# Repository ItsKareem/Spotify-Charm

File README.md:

# Spotify Charm ⋆ ݁ ♫ .

note: I still haven't done the Spotify API code for this. I just shipped it now for the [Arcana](https://arcana.hackclub.com/) deadline.

This Spotify Charm is a palm-sized, fully functional hardware display and controller that uses Spotify, designed with a retro aesthetic inspired by old-school MP3 players. I want to built this irl and use clay and paint to gice it a seashell shap and use actual seashells and use custom jewelery and bead kits to make it an actual charm. I feel like it would be fun to use this instead of my phone. I was inspired by online videos of people making their own creative hardware and physical media projects!

## Features
- Wemos ESP32-C3 Mini development board acting as the main controller
- Rotary Encoder for volume control
- Triple Button Layout ◁ㅤ ❚❚ ㅤ▷ (+ a power switch)
- uses a LiPo Battery Support with full power management circuitry
- Custom 3D-Printed Case featuring a 9cm diameter circular design

### 3D Case:

### Front:

### Back:

### PCB:

### Schematic (1. Baterry Management):

### Schematic (2. Push Buttons and Rotary Encoder):

### Schematic (3. ESP32 C3):

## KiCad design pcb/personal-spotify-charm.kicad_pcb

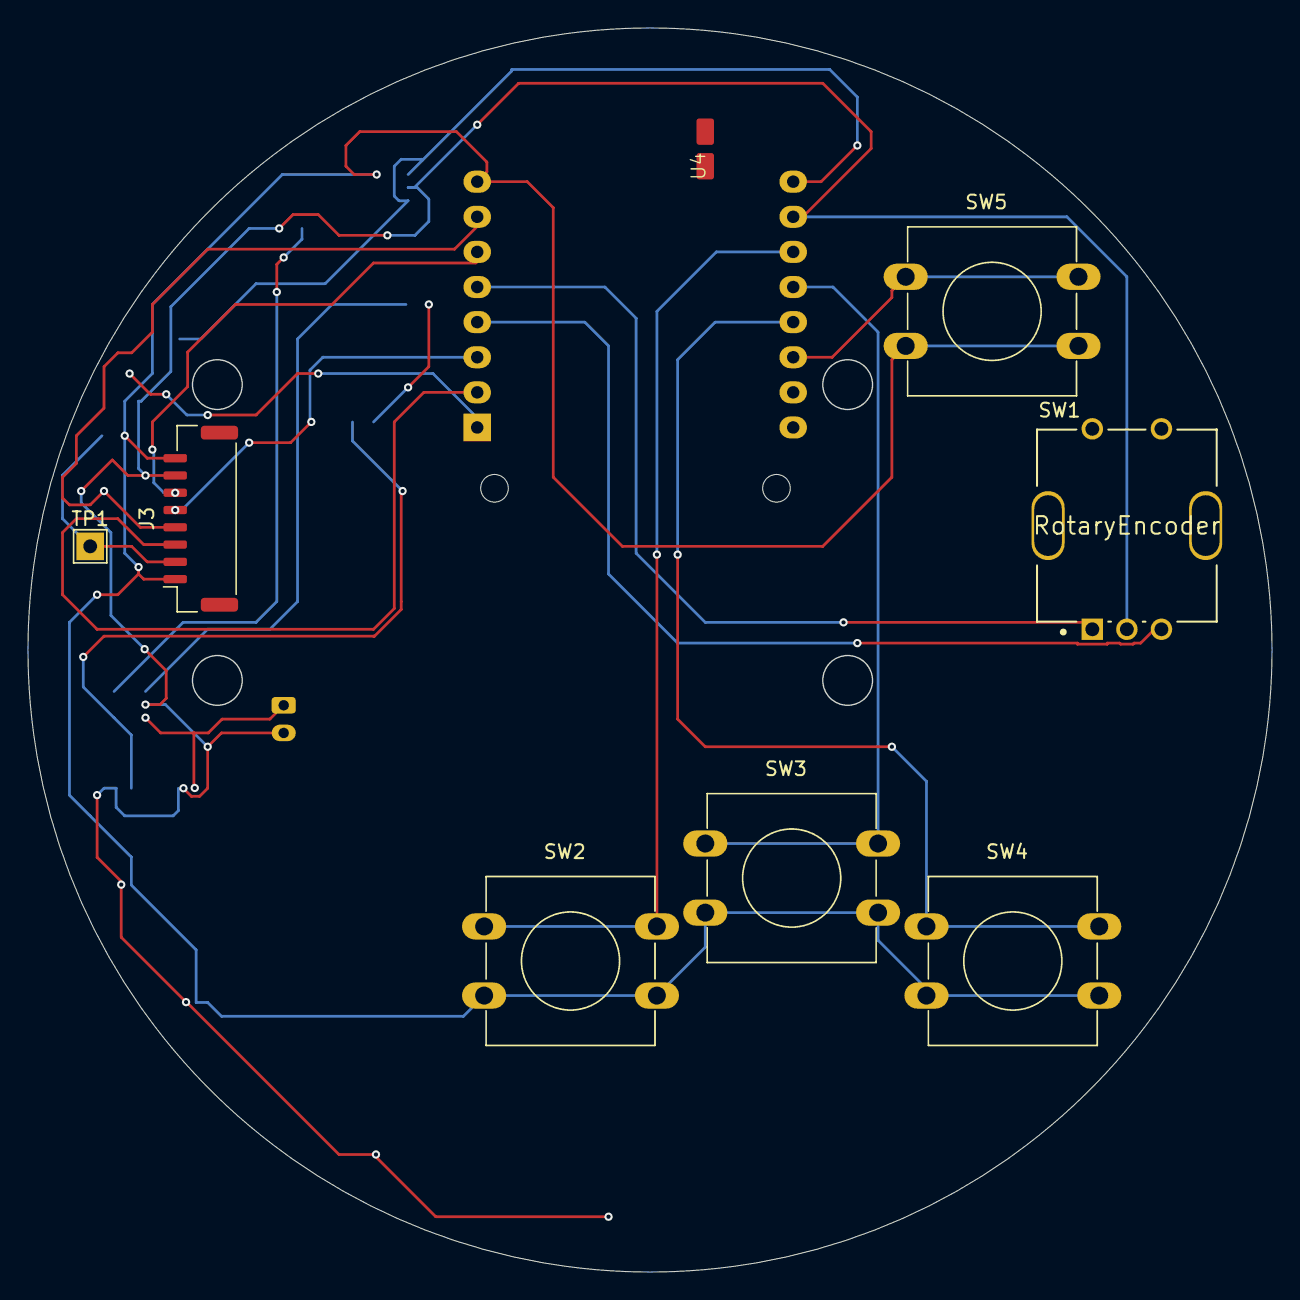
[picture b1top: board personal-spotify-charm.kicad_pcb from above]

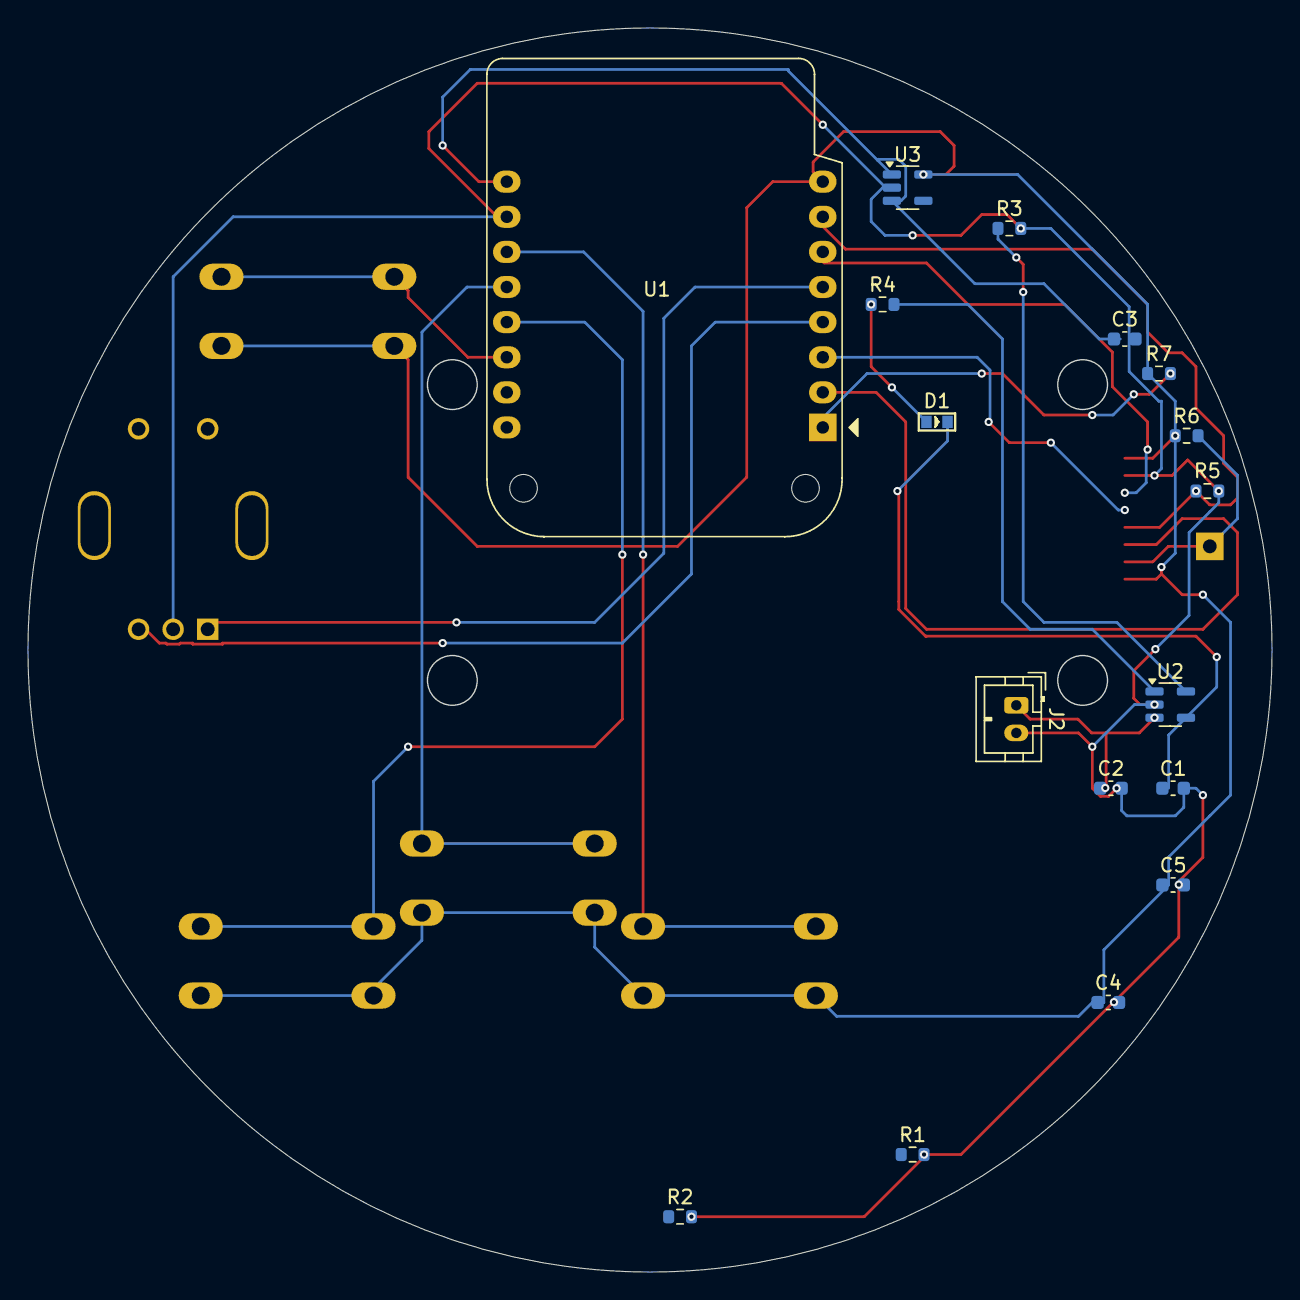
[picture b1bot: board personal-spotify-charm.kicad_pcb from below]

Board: 2 copper layers, 90.0 x 90.0 mm, 25 parts (17 on the bottom side), 20 nets.

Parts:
C1, C2: 4.7uF; C_0603_1608Metric
C3, C4: 10uF; C_0603_1608Metric
C5: 100nF; C_0603_1608Metric
D1: Blue (Charge); LED-0603
J2: Battery (JST-PH); JST_PH_B2B-PH-K_1x02_P2.00mm_Vertical
J3: Conn_01x08; JST_GH_SM08B-GHS-TB_1x08-1MP_P1.25mm_Horizontal
R1, R2: 5.1k; R_0603_1608Metric
R3: 2k; R_0603_1608Metric
R4: 470; R_0603_1608Metric
R5, R6, R7: 10k; R_0603_1608Metric
SW1: RotaryEncoder; Rotary Encoder bruh
SW2, SW3, SW4, SW5: SW_Push; SW_PUSH-12mm
TP1: TestPoint; TestPoint_THTPad_2.0x2.0mm_Drill1.0mm
U1: WEMOS_C3_mini
U2: MCP73831-2-OT; SOT-23-5
U3: ME6211C33M5; SOT-23-5
U4: Battery_Guage

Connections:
+3V3: C4.1, C5.1, J3.1, J3.8, R6.1, R7.1, SW2.2, SW3.2, SW4.2, SW5.2, U1.8 (3V3), U3.5 (V_{OUT})
+5V: C1.1, D1.2 (A), U2.4 (V_{DD})
+BATT: C2.1, J2.1, U2.3 (V_{BAT})
CLK: J3.5, U1.3 (D2)
CS: J3.4, R5.1, U1.7 (D5)
DC: J3.3, U1.2 (D3)
DIN: J3.6, U1.6 (D4)
EN: R7.2, U1.1 (EN)
GND: C1.2, C2.2, C3.2, C4.2, C5.2, J2.2, J3.7, R1.2, R2.2, R3.2, R5.2, SW1.C, U1.10 (GND), U2.2 (V_{SS}), U3.2 (V_{SS})
IO0: SW1.A, U1.5 (D0)
IO1: SW1.B, U1.4 (D1)
IO6: SW2.1, U1.11 (D6)
IO7: SW3.1, U1.12 (D7)
IO8: SW4.1, U1.13 (D8)
IO10: SW5.1, U1.14 (D10)
unnamed: D1.1 (K), R4.1
unnamed: J3.2, R6.2, TP1.1
unnamed: R3.1, U2.5 (PROG)
unnamed: R4.2, U2.1 (STAT)
VBUS: C3.1, U1.9 (VBus), U3.1 (V_{IN}), U3.3 (CE)

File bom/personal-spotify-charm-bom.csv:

Reference,Qty,Value,Price (USD),Footprint,Datasheet
"C1,C2",2,4.7uF,0.4,Capacitor_SMD:C_0603_1608Metric,~
"C3,C4",2,10uF,0.4,Capacitor_SMD:C_0603_1608Metric,~
C5,1,100nF,0.1,Capacitor_SMD:C_0603_1608Metric,~
D1,1,Blue (Charge),0.1,OPL_Optoelectronics:LED-0603,~
J2,1,Battery (JST-PH),0.75,Connector_JST:JST_PH_B2B-PH-K_1x02_P2.00mm_Vertical,~
J3,1,Conn_01x08,0.4,Connector_JST:JST_GH_SM08B-GHS-TB_1x08-1MP_P1.25mm_Horizontal,~
R3,1,2k,0.01,Resistor_SMD:R_0603_1608Metric,~
R4,1,470,0.01,Resistor_SMD:R_0603_1608Metric,~
"R5,R6,R7",3,10k,0.03,Resistor_SMD:R_0603_1608Metric,~
SW1,1,RotaryEncoder,0.5,Rotary_Encoder:Rotary Encoder bruh,~
"SW2,SW3,SW4,SW5",4,SW_Push,2,Button_Switch_THT:SW_PUSH-12mm,~
U1,1,WEMOS_C3_mini,9,RF_Module:WEMOS_C3_mini,https://www.wemos.cc/en/latest/c3/c3_mini.html
U2,1,MCP73831-2-OT,$0.85 ,Package_TO_SOT_SMD:SOT-23-5,http://ww1.microchip.com/downloads/en/DeviceDoc/20001984g.pdf
U3,1,ME6211C33M5,0.15,Package_TO_SOT_SMD:SOT-23-5,https://www.lcsc.com/datasheet/lcsc_datasheet_2304140030_MIC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
U4,1,~,2,ME:Battery_Guage,
Total,,,,,
